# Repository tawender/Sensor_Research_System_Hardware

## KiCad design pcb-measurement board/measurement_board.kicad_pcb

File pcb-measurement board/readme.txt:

measurement_board rev.1 layer output file descriptions

filename						description
---------------------------------------------------------------------------
measurement_board-F.SilkS.gto		top silkscreen
measurement_board-F.Paste.gtp		top solderpaste
measurement_board-F.Mask.gts		top soldermask
measurement_board-F.Cu.gtl			top copper
measurement_board-In1.Cu.g2			mid layer 1 copper
measurement_board-In2.Cu.g3			mid layer 2 copper
measurement_board-B.Cu.gbl			bottom copper
measurement_board-B.Mask.gbs		bottom soldermask
measurement_board-B.Paste.gbp		bottom solderpaste
measurement_board-B.SilkS.gbo		bottom silkscreen
measurement_board-Edge.Cuts.gm1		board outline
measurement_board.drl				NC Drill File
measurement_board_rev1_BOM.xls		Bill of Materials
measurement_board-all.pos			pick-and-place

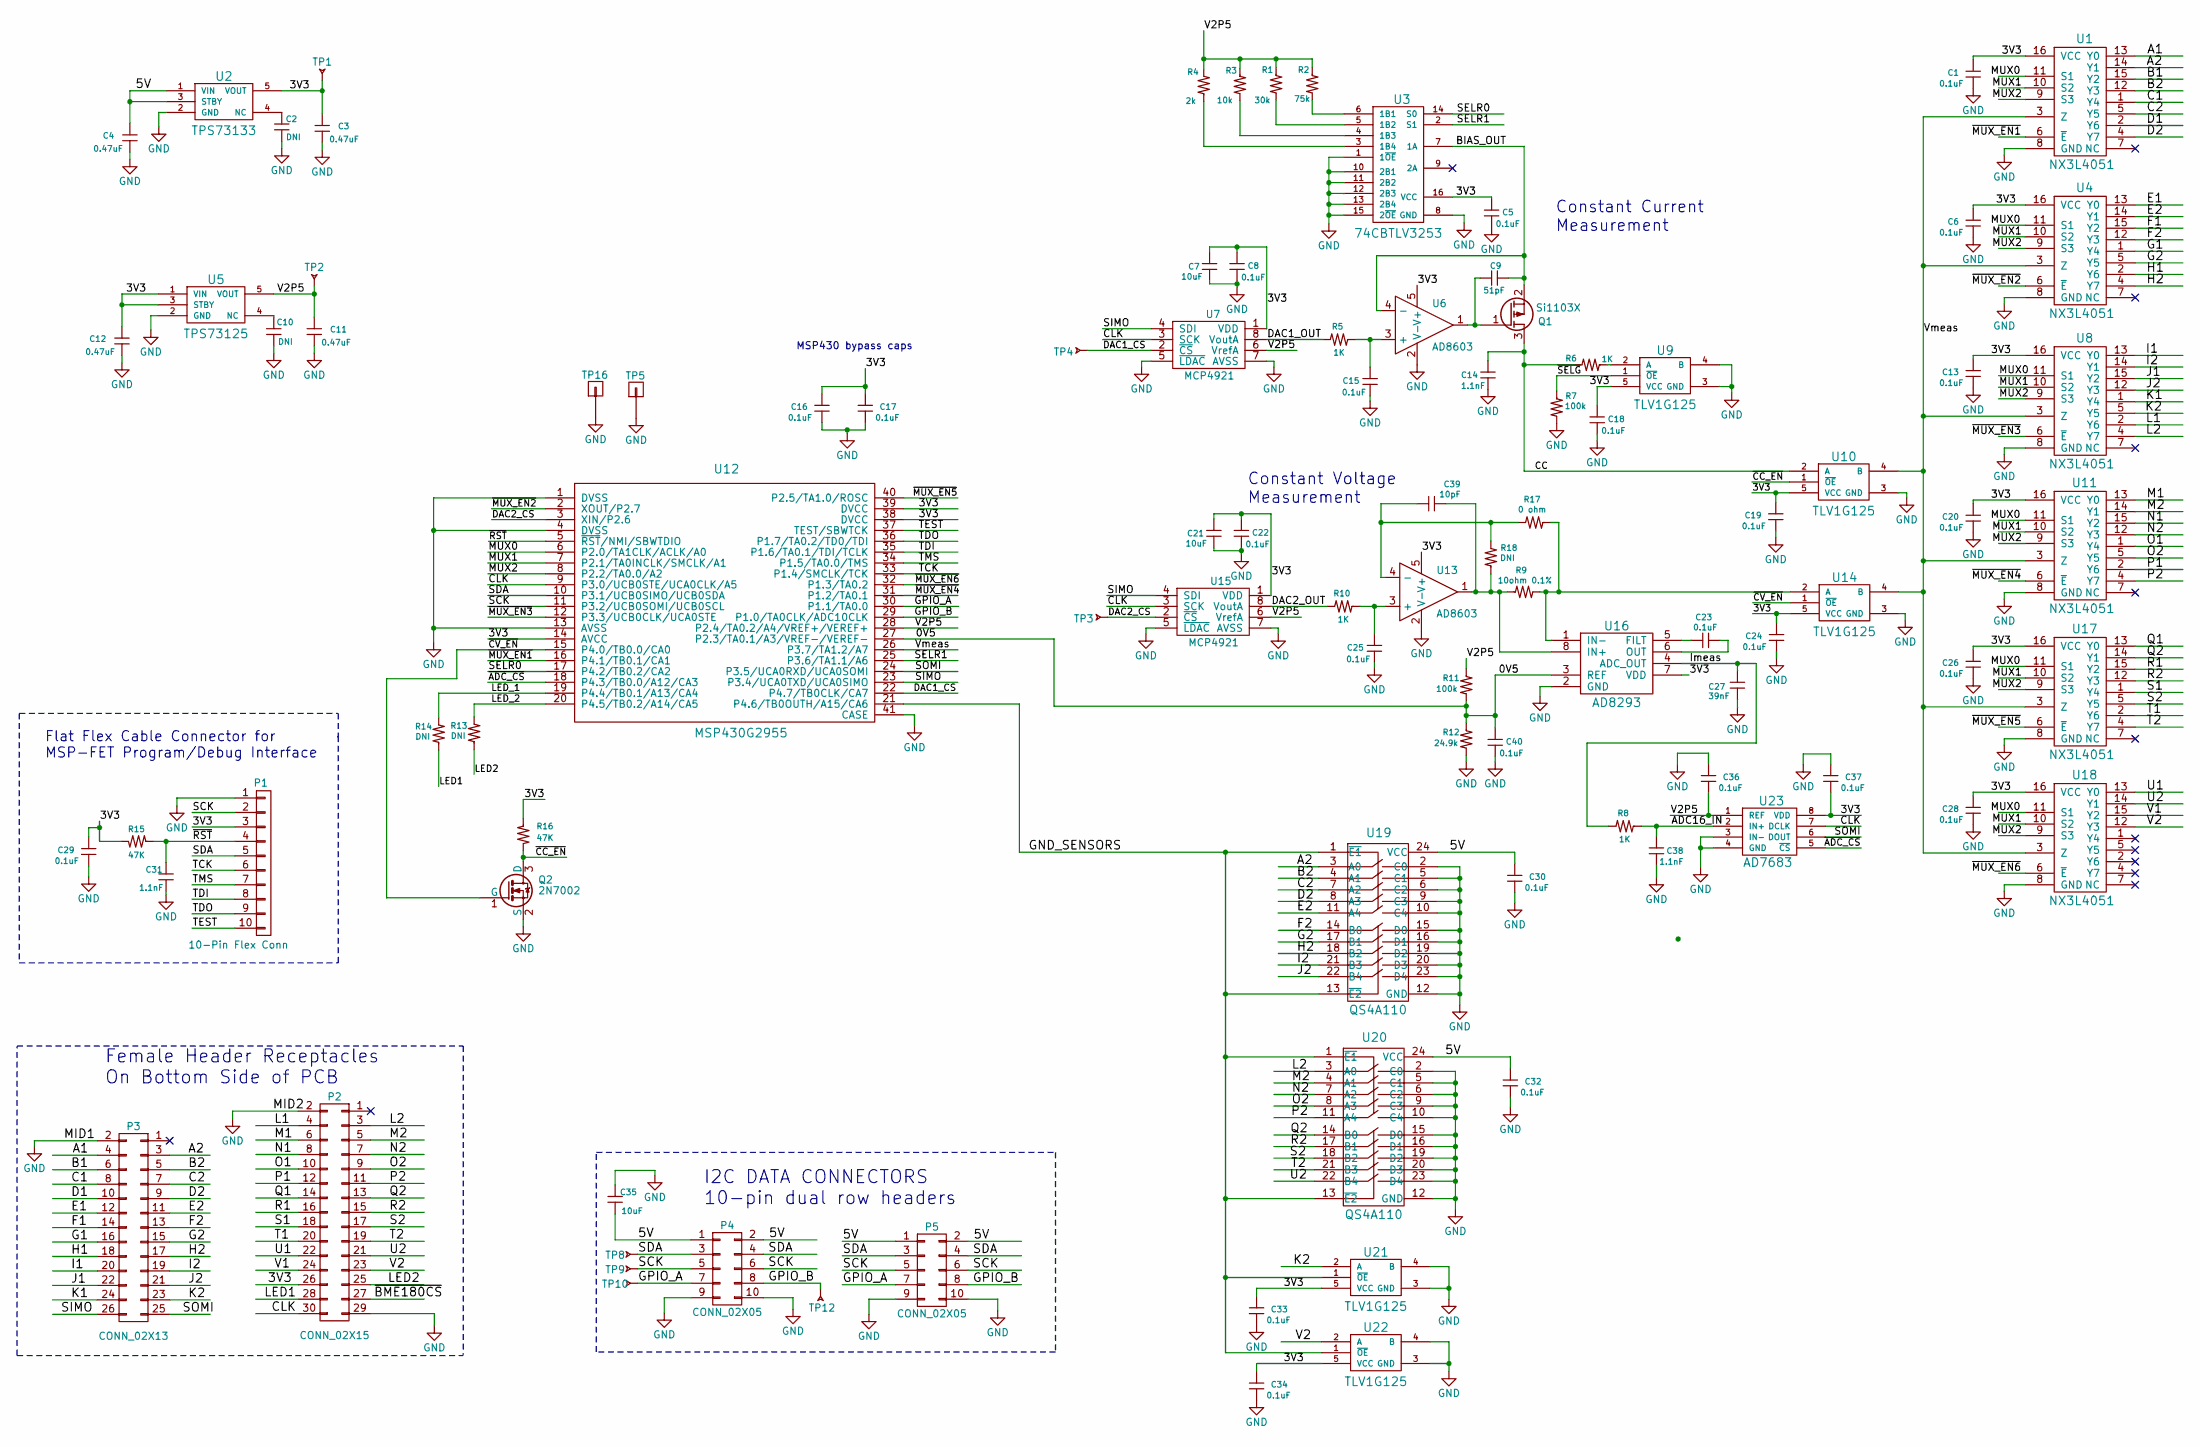
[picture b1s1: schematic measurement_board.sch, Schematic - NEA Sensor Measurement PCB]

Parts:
C1, C5, C6, C8, C13, C15, C16, C17, C18, C19, C20, C22, C23, C24, C25, C26, C28, C29, C36, C37, C40: 0.1uF; 0603; manufacturer pn GRM188R71C104KA01D
C2, C10: DNI; 0603; manufacturer pn NA
C3, C4, C11, C12: 0.47uF; 0603; manufacturer pn CL10A474KP8NNNC
C7, C21, C35: 10uF; 0603; manufacturer pn GRM188R60J106ME47D
C9: 51pF; 0603; manufacturer pn GRM1885C1H510JA01D
C14, C31, C38: 1.1nF; 0603; manufacturer pn GRM1885C1H112JA01D
C27: 39nF; 0603; manufacturer pn C0603C393K4RACTU
C30, C32, C33, C34: 0.1uF; R_0603_HandSoldering; manufacturer pn GRM188R71C104KA01D
C39: 10pF; 0402; manufacturer pn GRM1555C1H100JA01D
P1: 10-Pin Flex Conn; WM6745-FPC; manufacturer pn 0512811094
P2: CONN_02X15; Pin_Header_Straight_2x15_Pitch2.54mm; manufacturer pn 1-534998-5
P3: CONN_02X13; Pin_Header_Straight_2x13_Pitch2.54mm; manufacturer pn 1-534998-3
P4: CONN_02X05; header_2x5_idc; manufacturer pn PREC040DAAN-RC
P5: CONN_02X05; header_2x5_idc
Q1: Si1103X; SOT23; manufacturer pn SI1013X-T1-GE3
Q2: 2N7002; SOT23; manufacturer pn 2N7002-7-F
R1: 30k; 0603; manufacturer pn RC0603FR-0730KL
R2: 75k; 0603; manufacturer pn RC0603FR-0775KL
R3: 10k; 0603; manufacturer pn RC0603FR-0710KL
R4: 2k; 0603; manufacturer pn RC0603FR-072KL
R5, R6, R8, R10: 1K; 0603; manufacturer pn RC0603FR-071KLL
R7, R11: 100k; 0603; manufacturer pn RC0603FR-07100KL
R9: 10ohm 0.1%; 0805; manufacturer pn 2-1625868-7
R12: 24.9k; 0603; manufacturer pn RC0603FR-0724K9L
R13, R14: DNI; 0603
R15, R16: 47K; 0603; manufacturer pn RC0603FR-0747KL
R17: 0 ohm; 0402; manufacturer pn RC0402JR-070RL
R18: DNI; 0402; manufacturer pn RC0402JR-070RL
TP1, TP2, TP3, TP4, TP8, TP9, TP10, TP12: TP_SMT; TP_SMT.02
TP5, TP16: header_pin; Header_Pin_Rnd
U1, U4, U8, U11, U17, U18: NX3L4051; TSSOP16; manufacturer pn NX3L4051PW-118
U2: TPS73133; SOT23-5; manufacturer pn TPS73133DBVR
U3: 74CBTLV3253; DHVQFN16; manufacturer pn 74CBTLV3253BQ-115
U5: TPS73125; SOT23-5; manufacturer pn TPS73125DBVT
U6, U13: AD8603; SOT23-5; manufacturer pn AD8603AUJZ-REEL7
U7, U15: MCP4921; MSOP-8; manufacturer pn MCP4921T-E/MS
U9, U10, U14, U21, U22: TLV1G125; SOT23-5; manufacturer pn SN74CBTLV1G125DBVR
U12: MSP430G2955; VQFN40; manufacturer pn MSP430G2955IRHA40R
U16: AD8293; SOT23-8; manufacturer pn AD8293G160ARJZ-R7
U19, U20: QS4A110; QSOP-24; manufacturer pn QS4A110QG
U23: AD7683; RM-8; manufacturer pn AD7683ARMZRL7

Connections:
/0V5: C40.1, R11.1, R12.2, U12.27 (P2.3/TA0.1/A3/VREF-/VEREF-), U16.3 (REF)
/3V3: C1.1, C3.1, C5.1, C6.1, C7.1, C8.1, C12.1, C13.1, C16.1, C17.1, C18.1, C19.1, C20.1, C21.1, C22.1, C24.1, C26.1, C28.1, C29.1, C33.1, C34.1, C37.2, P1.3, P2.26, R15.1, R16.2, TP1.1, U1.16 (VCC), U2.5 (VOUT), U3.16 (VCC), U4.16 (VCC), U5.1 (VIN), U5.3 (STBY), U6.5 (V+), U7.1 (VDD), U8.16 (VCC), U9.5 (VCC), U10.5 (VCC), U11.16 (VCC), U12.14 (AVCC), U12.38 (DVCC), U12.39 (DVCC), U13.5 (V+), U14.5 (VCC), U15.1 (VDD), U16.7 (VDD), U17.16 (VCC), U18.16 (VCC), U21.5 (VCC), U22.5 (VCC), U23.8 (VDD)
/5V: C4.1, C30.1, C32.1, C35.2, P4.1, P4.2, P5.1, P5.2, U2.1 (VIN), U2.3 (STBY), U19.24 (VCC), U20.24 (VCC)
/A1: P3.4, U1.13 (Y0)
/A2: P3.3, U1.14 (Y1), U19.3 (A0)
/ADC16_IN: C38.1, R8.2, U23.2 (IN+)
/B1: P3.6, U1.15 (Y2)
/B2: P3.5, U1.12 (Y3), U19.4 (A1)
/BIAS_OUT: C9.1, Q1.2 (S), U3.7 (1A), U6.4 (-)
/C1: P3.8, U1.1 (Y4)
/C2: P3.7, U1.5 (Y5), U19.7 (A2)
/CC: C14.1, Q1.3 (D), R6.1, U10.2 (A)
/CLK: P2.30, U7.3 (SCK), U12.9 (P3.0/UCB0STE/UCA0CLK/A5), U15.3 (SCK), U23.7 (DCLK)
/D1: P3.10, U1.2 (Y6)
/D2: P3.9, U1.4 (Y7), U19.8 (A3)
/DAC1_CS: TP4.1, U7.2 (~CS~), U12.22 (P4.7/TB0CLK/CA7)
/DAC1_OUT: R5.1, U7.8 (VoutA)
/DAC2_CS: TP3.1, U12.3 (XIN/P2.6), U15.2 (~CS~)
/DAC2_OUT: R10.1, U15.8 (VoutA)
/E1: P3.12, U4.13 (Y0)
/E2: P3.11, U4.14 (Y1), U19.11 (A4)
/F1: P3.14, U4.15 (Y2)
/F2: P3.13, U4.12 (Y3), U19.14 (B0)
/G1: P3.16, U4.1 (Y4)
/G2: P3.15, U4.5 (Y5), U19.17 (B1)
/GND_SENSORS: U12.21 (P4.6/TB0OUTH/A15/CA6), U19.1 (~E1), U19.13 (~E2), U20.1 (~E1), U20.13 (~E2), U21.1 (~OE), U22.1 (~OE)
/GPIO_A: P4.7, P5.7, TP10.1, U12.30 (P1.1/TA0.0)
/GPIO_B: P4.8, P5.8, TP12.1, U12.29 (P1.0/TA0CLK/ADC10CLK)
/H1: P3.18, U4.2 (Y6)
/H2: P3.17, U4.4 (Y7), U19.18 (B2)
/I1: P3.20, U8.13 (Y0)
/I2: P3.19, U8.14 (Y1), U19.21 (B3)
/Imeas: C27.1, R8.1, U16.4 (ADC_OUT)
/J1: P3.22, U8.15 (Y2)
/J2: P3.21, U8.12 (Y3), U19.22 (B4)
/K1: P3.24, U8.1 (Y4)
/K2: P3.23, U8.5 (Y5), U21.2 (A)
/L1: P2.4, U8.2 (Y6)
/L2: P2.3, U8.4 (Y7), U20.3 (A0)
/LED1: P2.28, R14.2
/LED2: P2.25, R13.2
/LED_1: R14.1, U12.19 (P4.4/TB0.1/A13/CA4)
/LED_2: R13.1, U12.20 (P4.5/TB0.2/A14/CA5)
/M1: P2.6, U11.13 (Y0)
/M2: P2.5, U11.14 (Y1), U20.4 (A1)
/MUX0: U1.11 (S1), U4.11 (S1), U8.11 (S1), U11.11 (S1), U12.6 (P2.0/TA1CLK/ACLK/A0), U17.11 (S1), U18.11 (S1)
/MUX1: U1.10 (S2), U4.10 (S2), U8.10 (S2), U11.10 (S2), U12.7 (P2.1/TA0INCLK/SMCLK/A1), U17.10 (S2), U18.10 (S2)
/MUX2: U1.9 (S3), U4.9 (S3), U8.9 (S3), U11.9 (S3), U12.8 (P2.2/TA0.0/A2), U17.9 (S3), U18.9 (S3)
/N1: P2.8, U11.15 (Y2)
/N2: P2.7, U11.12 (Y3), U20.7 (A2)
/O1: P2.10, U11.1 (Y4)
/O2: P2.9, U11.5 (Y5), U20.8 (A3)
/P1: P2.12, U11.2 (Y6)
/P2: P2.11, U11.4 (Y7), U20.11 (A4)
/Q1: P2.14, U17.13 (Y0)
/Q2: P2.13, U17.14 (Y1), U20.14 (B0)
/R1: P2.16, U17.15 (Y2)
/R2: P2.15, U17.12 (Y3), U20.17 (B1)
/S1: P2.18, U17.1 (Y4)
/S2: P2.17, U17.5 (Y5), U20.18 (B2)
/SCK: P1.2, P4.5, P4.6, P5.5, P5.6, TP9.1, U12.11 (P3.2/UCB0SOMI/UCB0SCL)
/SDA: P1.5, P4.3, P4.4, P5.3, P5.4, TP8.1, U12.10 (P3.1/UCB0SIMO/UCB0SDA)
/SELR0: U3.14 (S0), U12.17 (P4.2/TB0.2/CA2)
/SELR1: U3.2 (S1), U12.25 (P3.6/TA1.1/A6)
/SIMO: P3.26, U7.4 (SDI), U12.23 (P3.4/UCA0TXD/UCA0SIMO), U15.4 (SDI)
/SOMI: P3.25, U12.24 (P3.5/UCA0RXD/UCA0SOMI), U23.6 (DOUT)
/T1: P2.20, U17.2 (Y6)
/T2: P2.19, U17.4 (Y7), U20.21 (B3)
/TCK: P1.6, U12.33 (P1.4/SMCLK/TCK)
/TDI: P1.8, U12.35 (P1.6/TA0.1/TDI/TCLK)
/TDO: P1.9, U12.36 (P1.7/TA0.2/TD0/TDI)
/TEST: P1.10, U12.37 (TEST/SBWTCK)
/TMS: P1.7, U12.34 (P1.5/TA0.0/TMS)
/U1: P2.22, U18.13 (Y0)
/U2: P2.21, U18.14 (Y1), U20.22 (B4)
/V1: P2.24, U18.15 (Y2)
/V2: P2.23, U18.12 (Y3), U22.2 (A)
/Vmeas: U1.3 (Z), U4.3 (Z), U8.3 (Z), U10.4 (B), U11.3 (Z), U12.26 (P3.7/TA1.2/A7), U14.4 (B), U17.3 (Z), U18.3 (Z)
/~ADC_CS: U12.18 (P4.3/TB0.0/A12/CA3), U23.5 (~CS)
/~BME180CS: P2.27
/~CC_EN: Q2.3 (D), R16.1, U10.1 (~OE)
/~CV_EN: Q2.1 (G), U12.15 (P4.0/TB0.0/CA0), U14.1 (~OE)
/~MUX_EN1: U1.6 (~E), U12.16 (P4.1/TB0.1/CA1)
/~MUX_EN2: U4.6 (~E), U12.2 (XOUT/P2.7)
/~MUX_EN3: U8.6 (~E), U12.12 (P3.3/UCB0CLK/UCA0STE)
/~MUX_EN4: U11.6 (~E), U12.31 (P1.2/TA0.1)
/~MUX_EN5: U12.40 (P2.5/TA1.0/ROSC), U17.6 (~E)
/~MUX_EN6: U12.32 (P1.3/TA0.2), U18.6 (~E)
/~RST: C31.1, P1.4, R15.2, U12.5 (~RST~/NMI/SBWTDIO)
/~SELG: R7.2, U9.1 (~OE)
GND: C1.2, C2.2, C3.2, C4.2, C5.2, C6.2, C7.2, C8.2, C10.2, C11.2, C12.2, C13.2, C14.2, C15.2, C16.2, C17.2, C18.2, C19.2, C20.2, C21.2, C22.2, C24.2, C25.2, C26.2, C27.2, C28.2, C29.2, C30.2, C31.2, C32.2, C33.2, C34.2, C35.1, C36.1, C37.1, C38.2, C40.2, P1.1, P2.2, P2.29, P3.2, P4.9, P4.10, P5.9, P5.10, Q2.2 (S), R7.1, R12.1, TP5.1, TP16.1, U1.8 (GND), U2.2 (GND), U3.1 (1~OE), U3.8 (GND), U3.10 (2B1), U3.11 (2B2), U3.12 (2B3), U3.13 (2B4), U3.15 (2~OE), U4.8 (GND), U5.2 (GND), U6.2 (V-), U7.5 (~LDAC~), U7.7 (AVSS), U8.8 (GND), U9.3 (GND), U9.4 (B), U10.3 (GND), U11.8 (GND), U12.1 (DVSS), U12.4 (DVSS), U12.13 (AVSS), U12.41 (CASE), U13.2 (V-), U14.3 (GND), U15.5 (~LDAC~), U15.7 (AVSS), U16.2 (GND), U17.8 (GND), U18.8 (GND), U19.2 (C0), U19.5 (C1), U19.6 (C2), U19.9 (C3), U19.10 (C4), U19.12 (GND), U19.15 (D0), U19.16 (D1), U19.19 (D2), U19.20 (D3), U19.23 (D4), U20.2 (C0), U20.5 (C1), U20.6 (C2), U20.9 (C3), U20.10 (C4), U20.12 (GND), U20.15 (D0), U20.16 (D1), U20.19 (D2), U20.20 (D3), U20.23 (D4), U21.3 (GND), U21.4 (B), U22.3 (GND), U22.4 (B), U23.3 (IN-), U23.4 (GND)
unnamed: C2.1, U2.4 (NC)
unnamed: C9.2, Q1.1 (G), U6.1
unnamed: C10.1, U5.4 (NC)
unnamed: C15.1, R5.2, U6.3 (+)
unnamed: C23.1, U16.6 (OUT)
unnamed: C23.2, U16.5 (FILT)
unnamed: C25.1, R10.2, U13.3 (+)
unnamed: C39.1, R9.2, R18.2, U13.1, U16.8 (IN+)
unnamed: C39.2, R17.1, R18.1, U13.4 (-)
unnamed: R1.1, U3.5 (1B2)
unnamed: R2.1, U3.6 (1B1)
unnamed: R3.1, U3.4 (1B3)
unnamed: R6.2, U9.2 (A)
unnamed: R9.1, R17.2, U14.2 (A), U16.1 (IN-)

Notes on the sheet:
MSP430 bypass caps
Female Header Receptacles On Bottom Side of PCB
Flat Flex Cable Connector for MSP-FET Program/Debug Interface
I2C DATA CONNECTORS 10-pin dual row headers
Constant Current Measurement
Constant Voltage Measurement

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
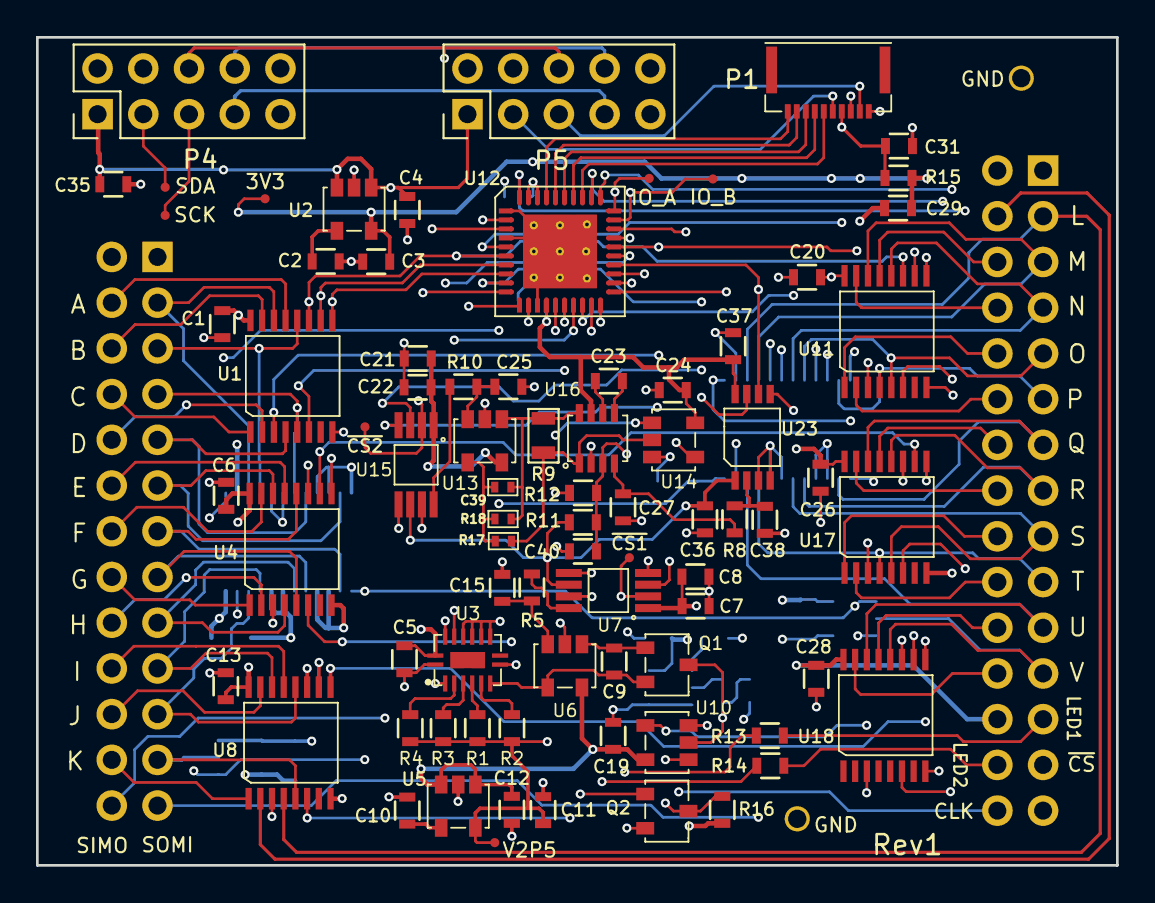
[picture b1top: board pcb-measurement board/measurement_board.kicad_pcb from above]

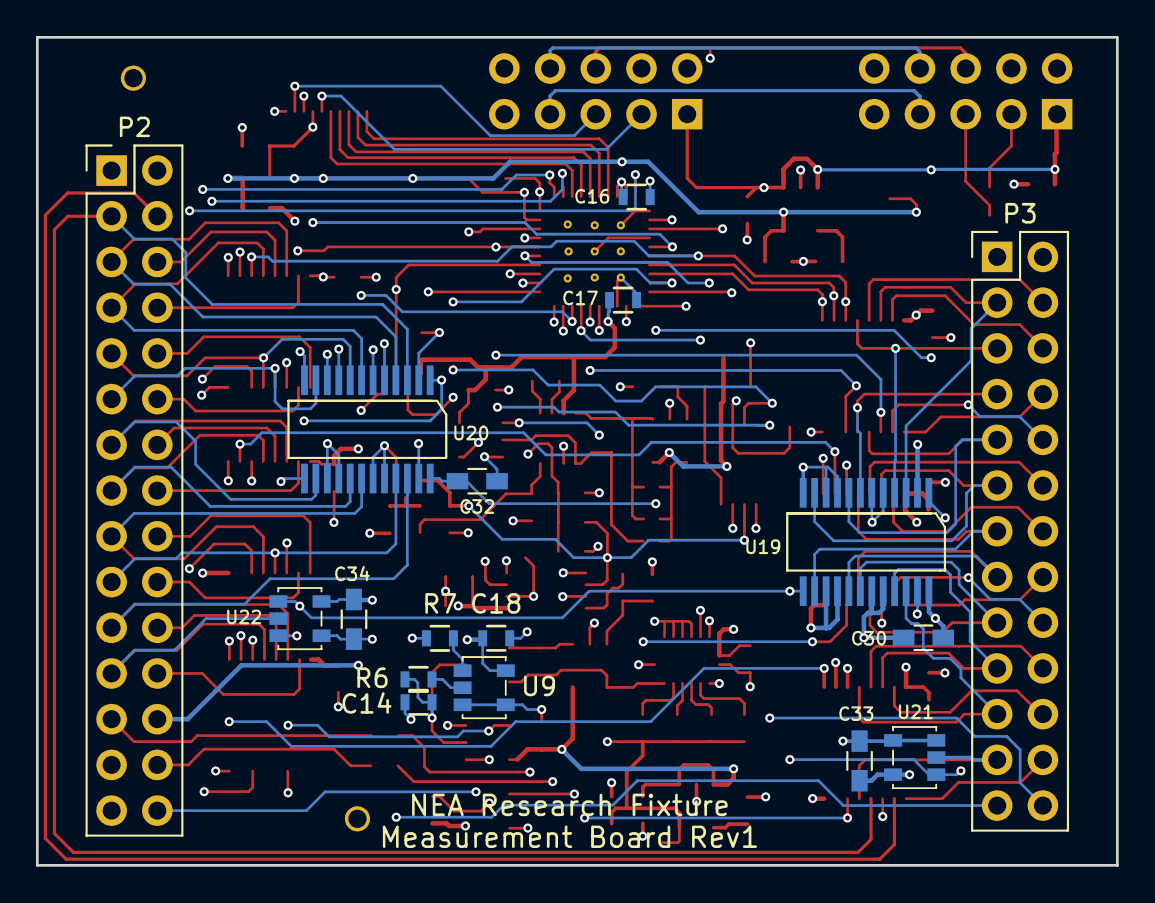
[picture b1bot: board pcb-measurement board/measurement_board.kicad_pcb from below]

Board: 4 copper layers, 60.0 x 46.0 mm, 98 parts (17 on the bottom side), 106 nets.

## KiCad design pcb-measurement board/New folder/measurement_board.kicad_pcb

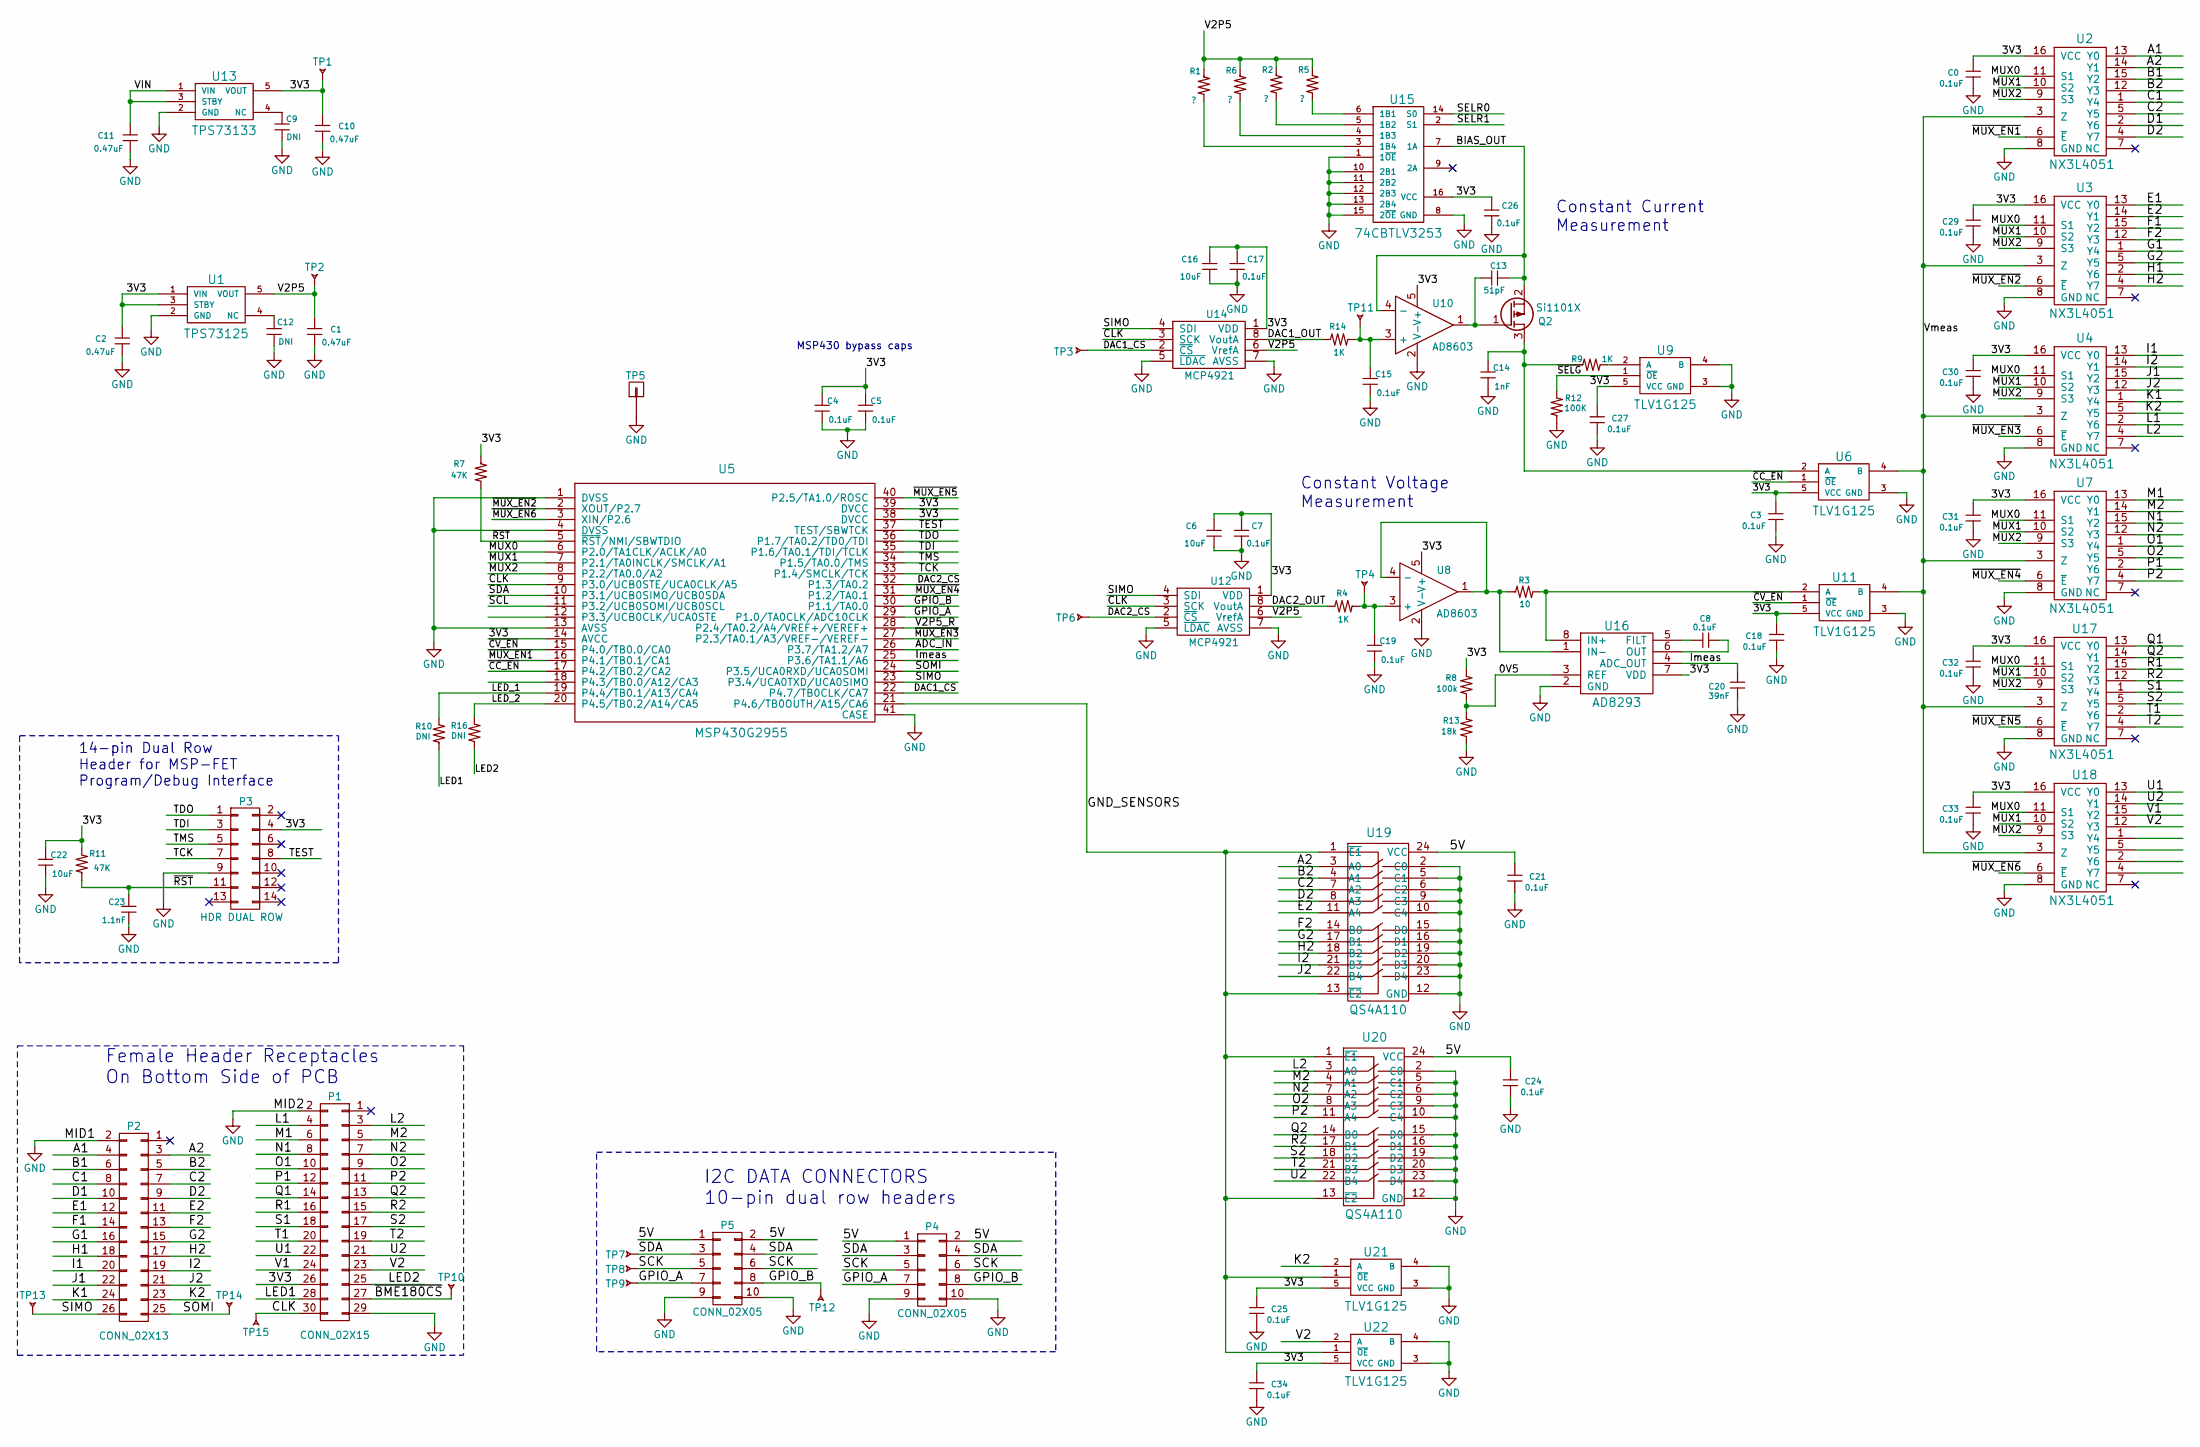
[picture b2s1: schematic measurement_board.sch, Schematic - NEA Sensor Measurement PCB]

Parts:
C0: 0.1uF; 0603; manufacturer pn GRM188R71C104KA01D
C1, C2, C10, C11: 0.47uF; 0603; manufacturer pn CL10A474KP8NNNC
C3, C18, C21, C24, C25, C27, C29, C30, C31, C32, C33, C34: 0.1uF; R_0603_HandSoldering; manufacturer pn GRM188R71C104KA01D
C4, C5, C7, C8, C15, C17, C19, C26: 0.1uF; 0402; manufacturer pn 0402YD104KAT2A
C6, C16: 10uF; 0402; manufacturer pn CL05A106MP8NUB8
C9, C12: DNI; 0603; manufacturer pn NA
C13: 51pF; 0402; manufacturer pn GRM1555C1H510JA01D
C14: 1nF; 0402; manufacturer pn GRM155R71H102KA01D
C20: 39nF; 0402; manufacturer pn 0402YD104KAT2A
C22: 10uF; 0402; manufacturer pn GRM155R60G106ME44D
C23: 1.1nF; 0402; manufacturer pn C0402C112J5GAC7867
P1: CONN_02X15; Pin_Header_Straight_2x15_Pitch2.54mm; manufacturer pn 2-146134-1
P2: CONN_02X13; Pin_Header_Straight_2x13_Pitch2.54mm; manufacturer pn 1-534998-5
P3: HDR DUAL ROW; Pin_Header_Straight_2x07_Pitch2.54mm; manufacturer pn PEC36DFAN
P4, P5: CONN_02X05; Pin_Header_Straight_2x05_Pitch2.54mm
Q2: Si1101X; SOT23; manufacturer pn SI1011X-T1-GE3
R1, R2, R5, R6: ?; 0603
R3: 10; 0402; manufacturer pn RC0402FR-07100KL
R4, R9, R14: 1K; 0402; manufacturer pn RC0402FR-071KL
R7: 47K; 0402; manufacturer pn RMCF0402FT47K0
R8: 100k; 0402; manufacturer pn RC0402FR-07100KL
R10, R16: DNI; 0603
R11: 47K; 0402; manufacturer pn RC0402FR-0747KL
R12: 100K; 0402; manufacturer pn RC0402FR-07100KL
R13: 18k; 0402; manufacturer pn RC0402FR-07100KL
TP1, TP2, TP3, TP4, TP6, TP7, TP8, TP9, TP10, TP11, TP12, TP13, TP14, TP15: TP_SMT; TP_SMT.02
TP5: header_pin; Header_Pin_Rnd
U1: TPS73125; SOT23-5; manufacturer pn TPS73125DBVT
U2, U3, U4, U7, U17, U18: NX3L4051; TSSOP16; manufacturer pn NX3L4051PW-118
U5: MSP430G2955; VQFN40; manufacturer pn MSP430G2955IRHA40R
U6, U9, U11, U21, U22: TLV1G125; SOT23-5; manufacturer pn SN74CBTLV1G125DBVR
U8, U10: AD8603; SOT23-5; manufacturer pn AD8603AUJZ-REEL7
U12, U14: MCP4921; MSOP-8; manufacturer pn MCP4921T-E/MS
U13: TPS73133; SOT23-5; manufacturer pn TPS73133DBVR
U15: 74CBTLV3253; DHVQFN16; manufacturer pn 74CBTLV3253BQ-115
U16: AD8293; SOT23-8; manufacturer pn AD8293G160ARJZ-R7
U19, U20: QS4A110; QSOP-24; manufacturer pn QS4A110QG

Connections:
/0V5: R8.1, R13.2, U16.3 (REF)
/3V3: C0.1, C2.1, C3.1, C4.1, C5.1, C6.1, C7.1, C10.1, C16.1, C17.1, C18.1, C22.1, C25.1, C26.1, C27.1, C29.1, C30.1, C31.1, C32.1, C33.1, C34.1, P1.26, P3.4, R7.2, R8.2, R11.1, TP1.1, U1.1 (VIN), U1.3 (STBY), U2.16 (VCC), U3.16 (VCC), U4.16 (VCC), U5.14 (AVCC), U5.38 (DVCC), U5.39 (DVCC), U6.5 (VCC), U7.16 (VCC), U8.5 (V+), U9.5 (VCC), U10.5 (V+), U11.5 (VCC), U12.1 (VDD), U13.5 (VOUT), U14.1 (VDD), U15.16 (VCC), U16.7 (VDD), U17.16 (VCC), U18.16 (VCC), U21.5 (VCC), U22.5 (VCC)
/5V: C21.1, C24.1, P4.1, P4.2, P5.1, P5.2, U19.24 (VCC), U20.24 (VCC)
/A1: P2.4, U2.13 (Y0)
/A2: P2.3, U2.14 (Y1), U19.3 (A0)
/ADC_IN: U5.26 (P3.7/TA1.2/A7)
/B1: P2.6, U2.15 (Y2)
/B2: P2.5, U2.12 (Y3), U19.4 (A1)
/BIAS_OUT: C13.1, Q2.2 (S), U10.4 (-), U15.7 (1A)
/C1: P2.8, U2.1 (Y4)
/C2: P2.7, U2.5 (Y5), U19.7 (A2)
/CLK: P1.30, TP15.1, U5.9 (P3.0/UCB0STE/UCA0CLK/A5), U12.3 (SCK), U14.3 (SCK)
/D1: P2.10, U2.2 (Y6)
/D2: P2.9, U2.4 (Y7), U19.8 (A3)
/DAC1_CS: TP3.1, U5.22 (P4.7/TB0CLK/CA7), U14.2 (~CS~)
/DAC1_OUT: R14.1, U14.8 (VoutA)
/DAC2_CS: TP6.1, U5.32 (P1.3/TA0.2), U12.2 (~CS~)
/DAC2_OUT: R4.1, U12.8 (VoutA)
/E1: P2.12, U3.13 (Y0)
/E2: P2.11, U3.14 (Y1), U19.11 (A4)
/F1: P2.14, U3.15 (Y2)
/F2: P2.13, U3.12 (Y3), U19.14 (B0)
/G1: P2.16, U3.1 (Y4)
/G2: P2.15, U3.5 (Y5), U19.17 (B1)
/GND_SENSORS: U5.21 (P4.6/TB0OUTH/A15/CA6), U19.1 (~E1), U19.13 (~E2), U20.1 (~E1), U20.13 (~E2), U21.1 (~OE), U22.1 (~OE)
/GPIO_A: P4.7, P5.7, TP9.1, U5.29 (P1.0/TA0CLK/ADC10CLK)
/GPIO_B: P4.8, P5.8, TP12.1, U5.30 (P1.1/TA0.0)
/H1: P2.18, U3.2 (Y6)
/H2: P2.17, U3.4 (Y7), U19.18 (B2)
/I1: P2.20, U4.13 (Y0)
/I2: P2.19, U4.14 (Y1), U19.21 (B3)
/Imeas: C20.1, U5.25 (P3.6/TA1.1/A6), U16.4 (ADC_OUT)
/J1: P2.22, U4.15 (Y2)
/J2: P2.21, U4.12 (Y3), U19.22 (B4)
/K1: P2.24, U4.1 (Y4)
/K2: P2.23, U4.5 (Y5), U21.2 (A)
/L1: P1.4, U4.2 (Y6)
/L2: P1.3, U4.4 (Y7), U20.3 (A0)
/LED1: P1.28, R10.2
/LED2: P1.25, R16.2
/LED_1: R10.1, U5.19 (P4.4/TB0.1/A13/CA4)
/LED_2: R16.1, U5.20 (P4.5/TB0.2/A14/CA5)
/M1: P1.6, U7.13 (Y0)
/M2: P1.5, U7.14 (Y1), U20.4 (A1)
/MUX0: U2.11 (S1), U3.11 (S1), U4.11 (S1), U5.6 (P2.0/TA1CLK/ACLK/A0), U7.11 (S1), U17.11 (S1), U18.11 (S1)
/MUX1: U2.10 (S2), U3.10 (S2), U4.10 (S2), U5.7 (P2.1/TA0INCLK/SMCLK/A1), U7.10 (S2), U17.10 (S2), U18.10 (S2)
/MUX2: U2.9 (S3), U3.9 (S3), U4.9 (S3), U5.8 (P2.2/TA0.0/A2), U7.9 (S3), U17.9 (S3), U18.9 (S3)
/N1: P1.8, U7.15 (Y2)
/N2: P1.7, U7.12 (Y3), U20.7 (A2)
/O1: P1.10, U7.1 (Y4)
/O2: P1.9, U7.5 (Y5), U20.8 (A3)
/P1: P1.12, U7.2 (Y6)
/P2: P1.11, U7.4 (Y7), U20.11 (A4)
/Q1: P1.14, U17.13 (Y0)
/Q2: P1.13, U17.14 (Y1), U20.14 (B0)
/R1: P1.16, U17.15 (Y2)
/R2: P1.15, U17.12 (Y3), U20.17 (B1)
/S1: P1.18, U17.1 (Y4)
/S2: P1.17, U17.5 (Y5), U20.18 (B2)
/SCK: P4.5, P4.6, P5.5, P5.6, TP8.1
/SCL: U5.11 (P3.2/UCB0SOMI/UCB0SCL)
/SDA: P4.3, P4.4, P5.3, P5.4, TP7.1, U5.10 (P3.1/UCB0SIMO/UCB0SDA)
/SELR0: U15.14 (S0)
/SELR1: U15.2 (S1)
/SIMO: P2.26, TP13.1, U5.23 (P3.4/UCA0TXD/UCA0SIMO), U12.4 (SDI), U14.4 (SDI)
/SOMI: P2.25, TP14.1, U5.24 (P3.5/UCA0RXD/UCA0SOMI)
/T1: P1.20, U17.2 (Y6)
/T2: P1.19, U17.4 (Y7), U20.21 (B3)
/TCK: P3.7, U5.33 (P1.4/SMCLK/TCK)
/TDI: P3.3, U5.35 (P1.6/TA0.1/TDI/TCLK)
/TDO: P3.1, U5.36 (P1.7/TA0.2/TD0/TDI)
/TEST: P3.8, U5.37 (TEST/SBWTCK)
/TMS: P3.5, U5.34 (P1.5/TA0.0/TMS)
/U1: P1.22, U18.13 (Y0)
/U2: P1.21, U18.14 (Y1), U20.22 (B4)
/V1: P1.24, U18.15 (Y2)
/V2: P1.23, U18.12 (Y3), U22.2 (A)
/V2P5: C1.1, R1.2, R2.2, R5.2, R6.2, TP2.1, U1.5 (VOUT), U12.6 (VrefA), U14.6 (VrefA)
/V2P5_R: U5.28 (P2.4/TA0.2/A4/VREF+/VEREF+)
/VIN: C11.1, U13.1 (VIN), U13.3 (STBY)
/Vmeas: U2.3 (Z), U3.3 (Z), U4.3 (Z), U6.4 (B), U7.3 (Z), U11.4 (B), U17.3 (Z), U18.3 (Z)
/~BME180CS: P1.27, TP10.1
/~CC_EN: U5.17 (P4.2/TB0.2/CA2), U6.1 (~OE)
/~CV_EN: U5.15 (P4.0/TB0.0/CA0), U11.1 (~OE)
/~MUX_EN1: U2.6 (~E), U5.16 (P4.1/TB0.1/CA1)
/~MUX_EN2: U3.6 (~E), U5.2 (XOUT/P2.7)
/~MUX_EN3: U4.6 (~E), U5.27 (P2.3/TA0.1/A3/VREF-/VEREF-)
/~MUX_EN4: U5.31 (P1.2/TA0.1), U7.6 (~E)
/~MUX_EN5: U5.40 (P2.5/TA1.0/ROSC), U17.6 (~E)
/~MUX_EN6: U5.3 (XIN/P2.6), U18.6 (~E)
/~RST: C23.1, P3.11, R7.1, R11.2, U5.5 (~RST~/NMI/SBWTDIO)
/~SELG: R12.1, U9.1 (~OE)
GND: C0.2, C1.2, C2.2, C3.2, C4.2, C5.2, C6.2, C7.2, C9.2, C10.2, C11.2, C12.2, C14.2, C15.2, C16.2, C17.2, C18.2, C19.2, C20.2, C21.2, C22.2, C23.2, C24.2, C25.2, C26.2, C27.2, C29.2, C30.2, C31.2, C32.2, C33.2, C34.2, P1.2, P1.29, P2.2, P3.9, P4.9, P4.10, P5.9, P5.10, R12.2, R13.1, TP5.1, U1.2 (GND), U2.8 (GND), U3.8 (GND), U4.8 (GND), U5.1 (DVSS), U5.4 (DVSS), U5.13 (AVSS), U5.41 (CASE), U6.3 (GND), U7.8 (GND), U8.2 (V-), U9.3 (GND), U9.4 (B), U10.2 (V-), U11.3 (GND), U12.5 (~LDAC~), U12.7 (AVSS), U13.2 (GND), U14.5 (~LDAC~), U14.7 (AVSS), U15.1 (1~OE), U15.8 (GND), U15.10 (2B1), U15.11 (2B2), U15.12 (2B3), U15.13 (2B4), U15.15 (2~OE), U16.2 (GND), U17.8 (GND), U18.8 (GND), U19.2 (C0), U19.5 (C1), U19.6 (C2), U19.9 (C3), U19.10 (C4), U19.12 (GND), U19.15 (D0), U19.16 (D1), U19.19 (D2), U19.20 (D3), U19.23 (D4), U20.2 (C0), U20.5 (C1), U20.6 (C2), U20.9 (C3), U20.10 (C4), U20.12 (GND), U20.15 (D0), U20.16 (D1), U20.19 (D2), U20.20 (D3), U20.23 (D4), U21.3 (GND), U21.4 (B), U22.3 (GND), U22.4 (B)
unnamed: C8.1, U16.5 (FILT)
unnamed: C8.2, U16.6 (OUT)
unnamed: C9.1, U13.4 (NC)
unnamed: C12.1, U1.4 (NC)
unnamed: C13.2, Q2.1 (G), U10.1
unnamed: C14.1, Q2.3 (D), R9.2, U6.2 (A)
unnamed: C15.1, R14.2, TP11.1, U10.3 (+)
unnamed: C19.1, R4.2, TP4.1, U8.3 (+)
unnamed: R1.1, U15.3 (1B4)
unnamed: R2.1, U15.5 (1B2)
unnamed: R3.1, U11.2 (A), U16.8 (IN+)
unnamed: R3.2, U8.1, U8.4 (-), U16.1 (IN-)
unnamed: R5.1, U15.6 (1B1)
unnamed: R6.1, U15.4 (1B3)
unnamed: R9.1, U9.2 (A)

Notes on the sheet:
MSP430 bypass caps
Female Header Receptacles On Bottom Side of PCB
14-pin Dual Row Header for MSP-FET Program/Debug Interface
I2C DATA CONNECTORS 10-pin dual row headers
Constant Current Measurement
Constant Voltage Measurement

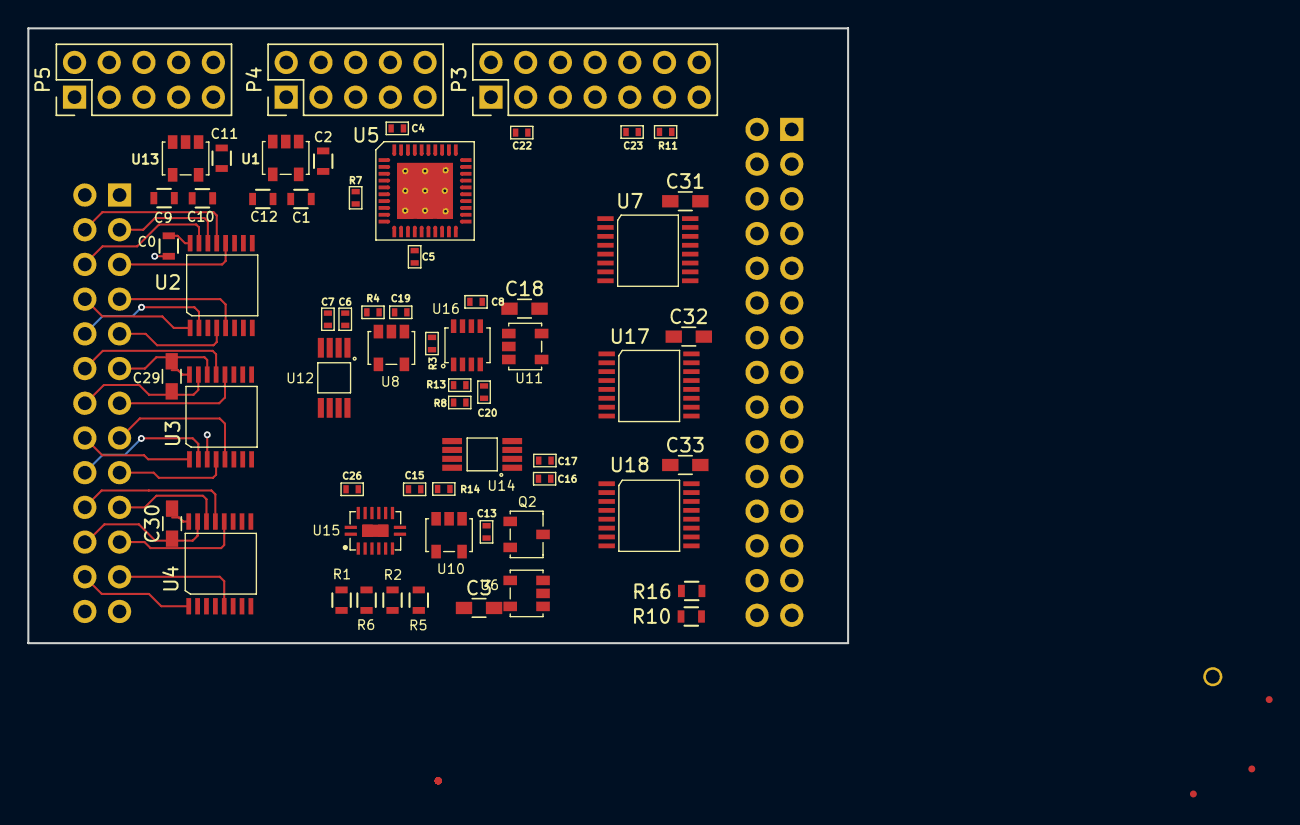
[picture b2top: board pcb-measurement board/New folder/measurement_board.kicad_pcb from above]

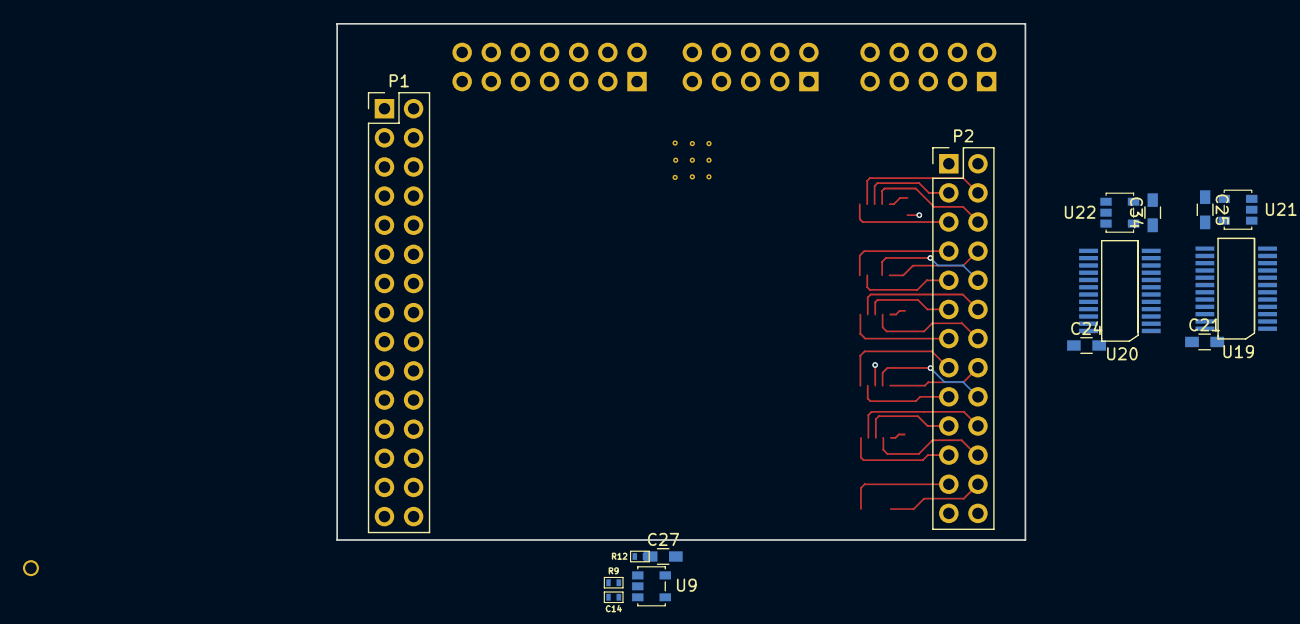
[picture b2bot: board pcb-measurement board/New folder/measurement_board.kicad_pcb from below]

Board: 4 copper layers, 60.0 x 45.0 mm, 92 parts (15 on the bottom side), 103 nets.
